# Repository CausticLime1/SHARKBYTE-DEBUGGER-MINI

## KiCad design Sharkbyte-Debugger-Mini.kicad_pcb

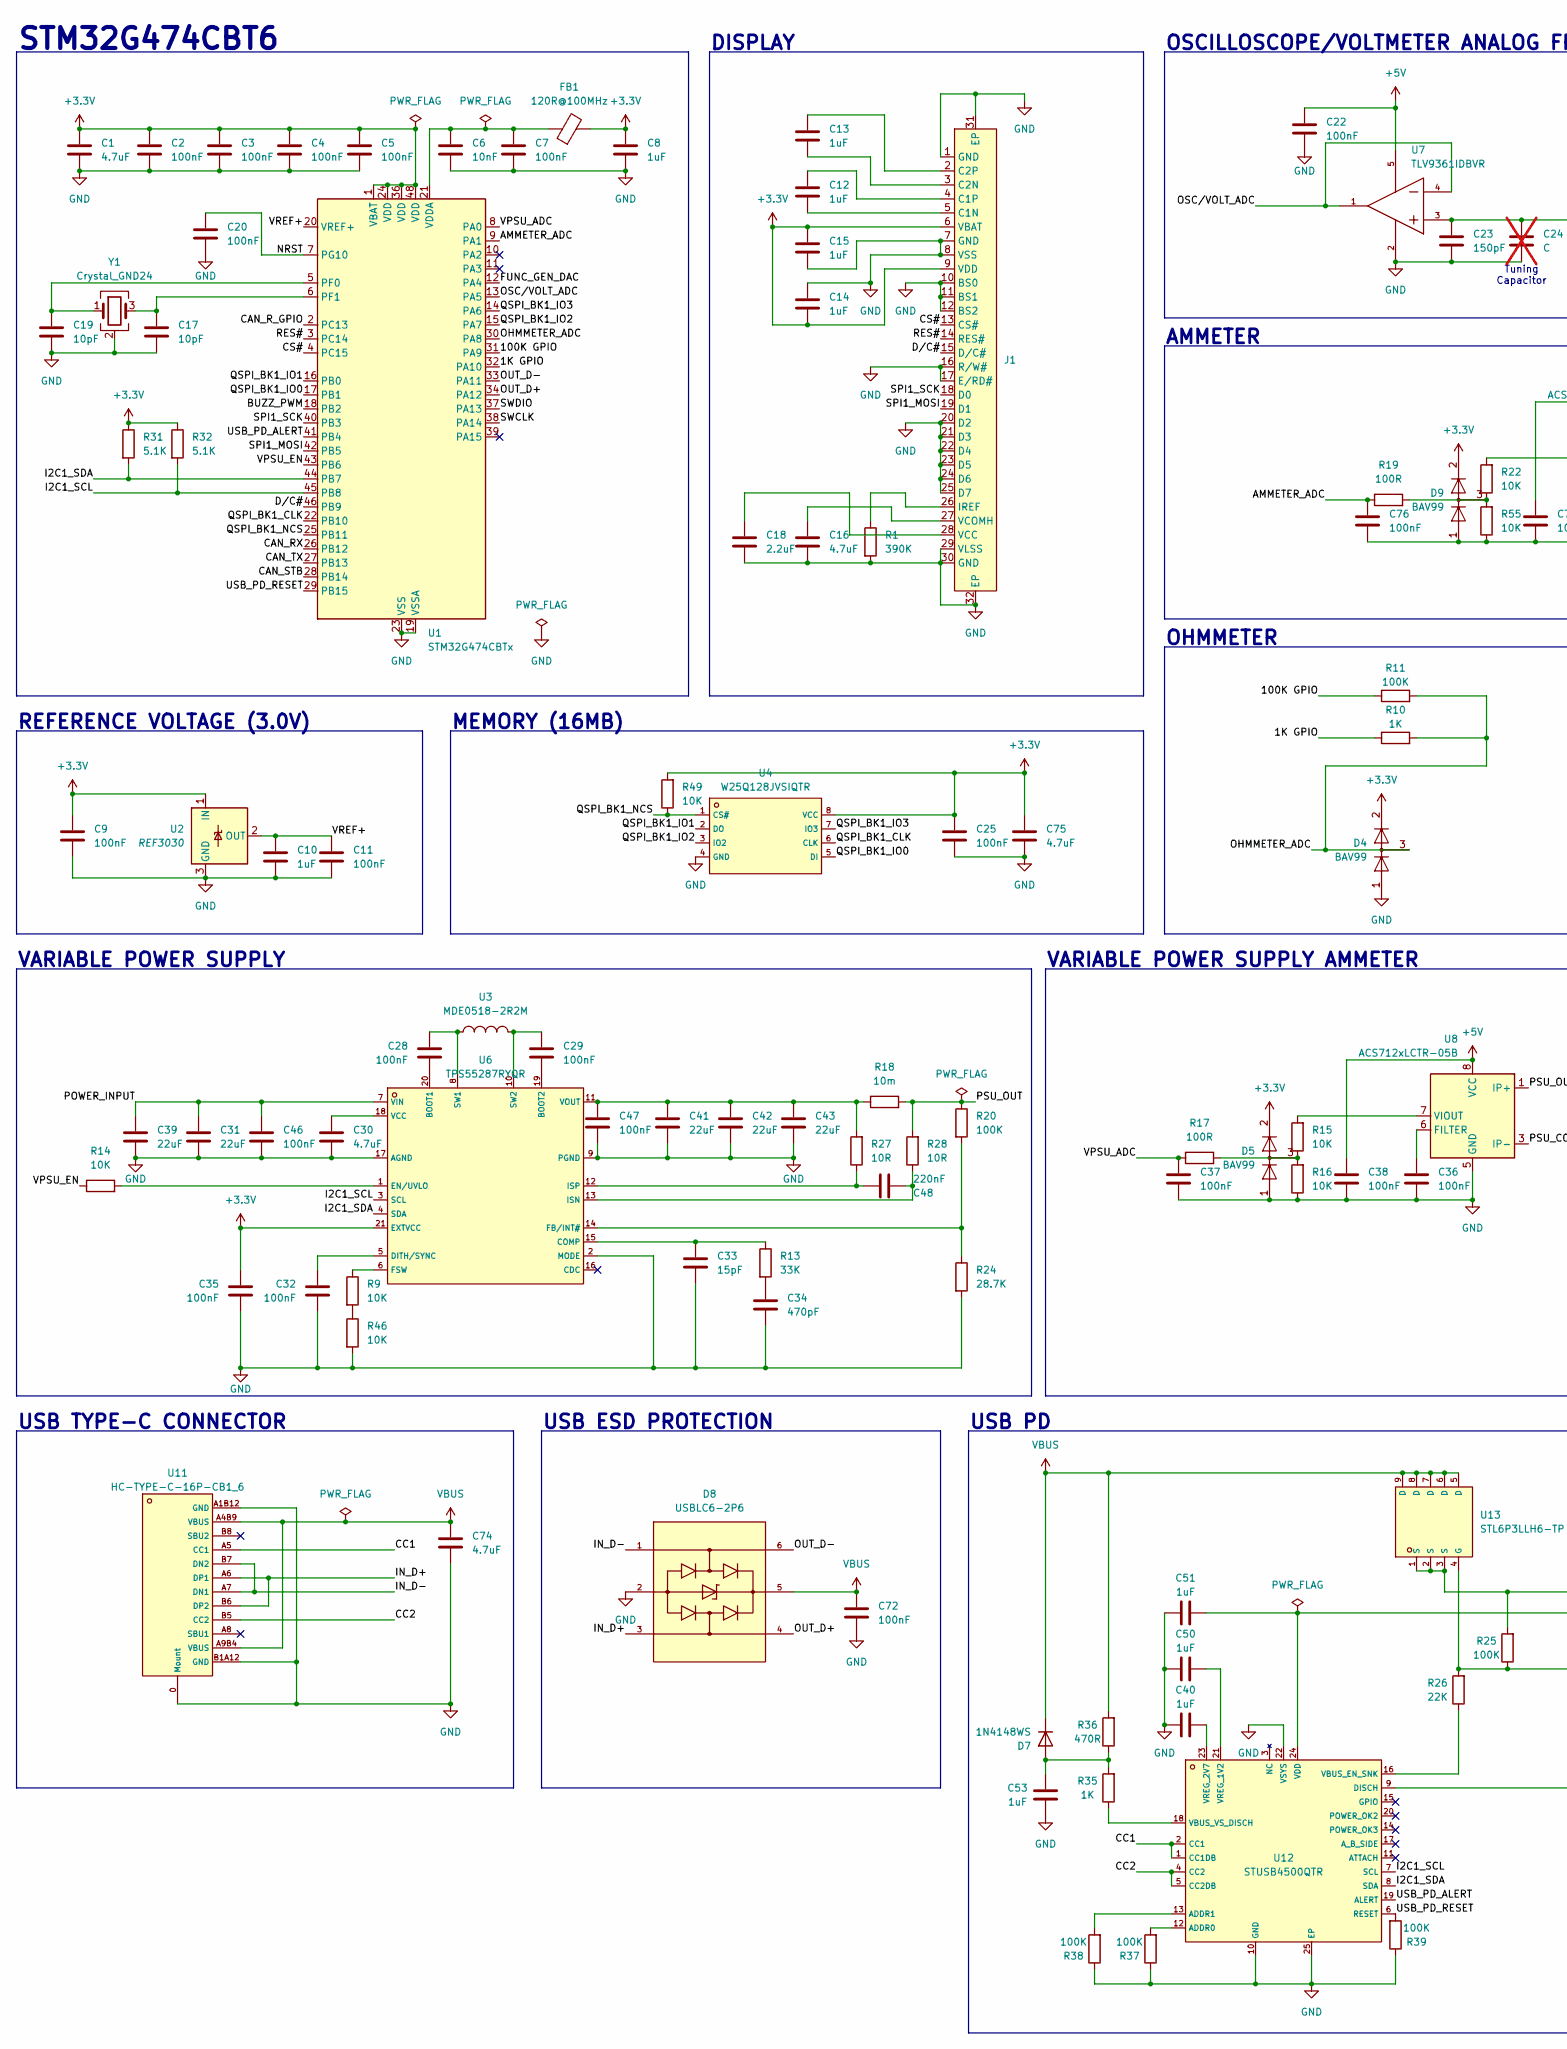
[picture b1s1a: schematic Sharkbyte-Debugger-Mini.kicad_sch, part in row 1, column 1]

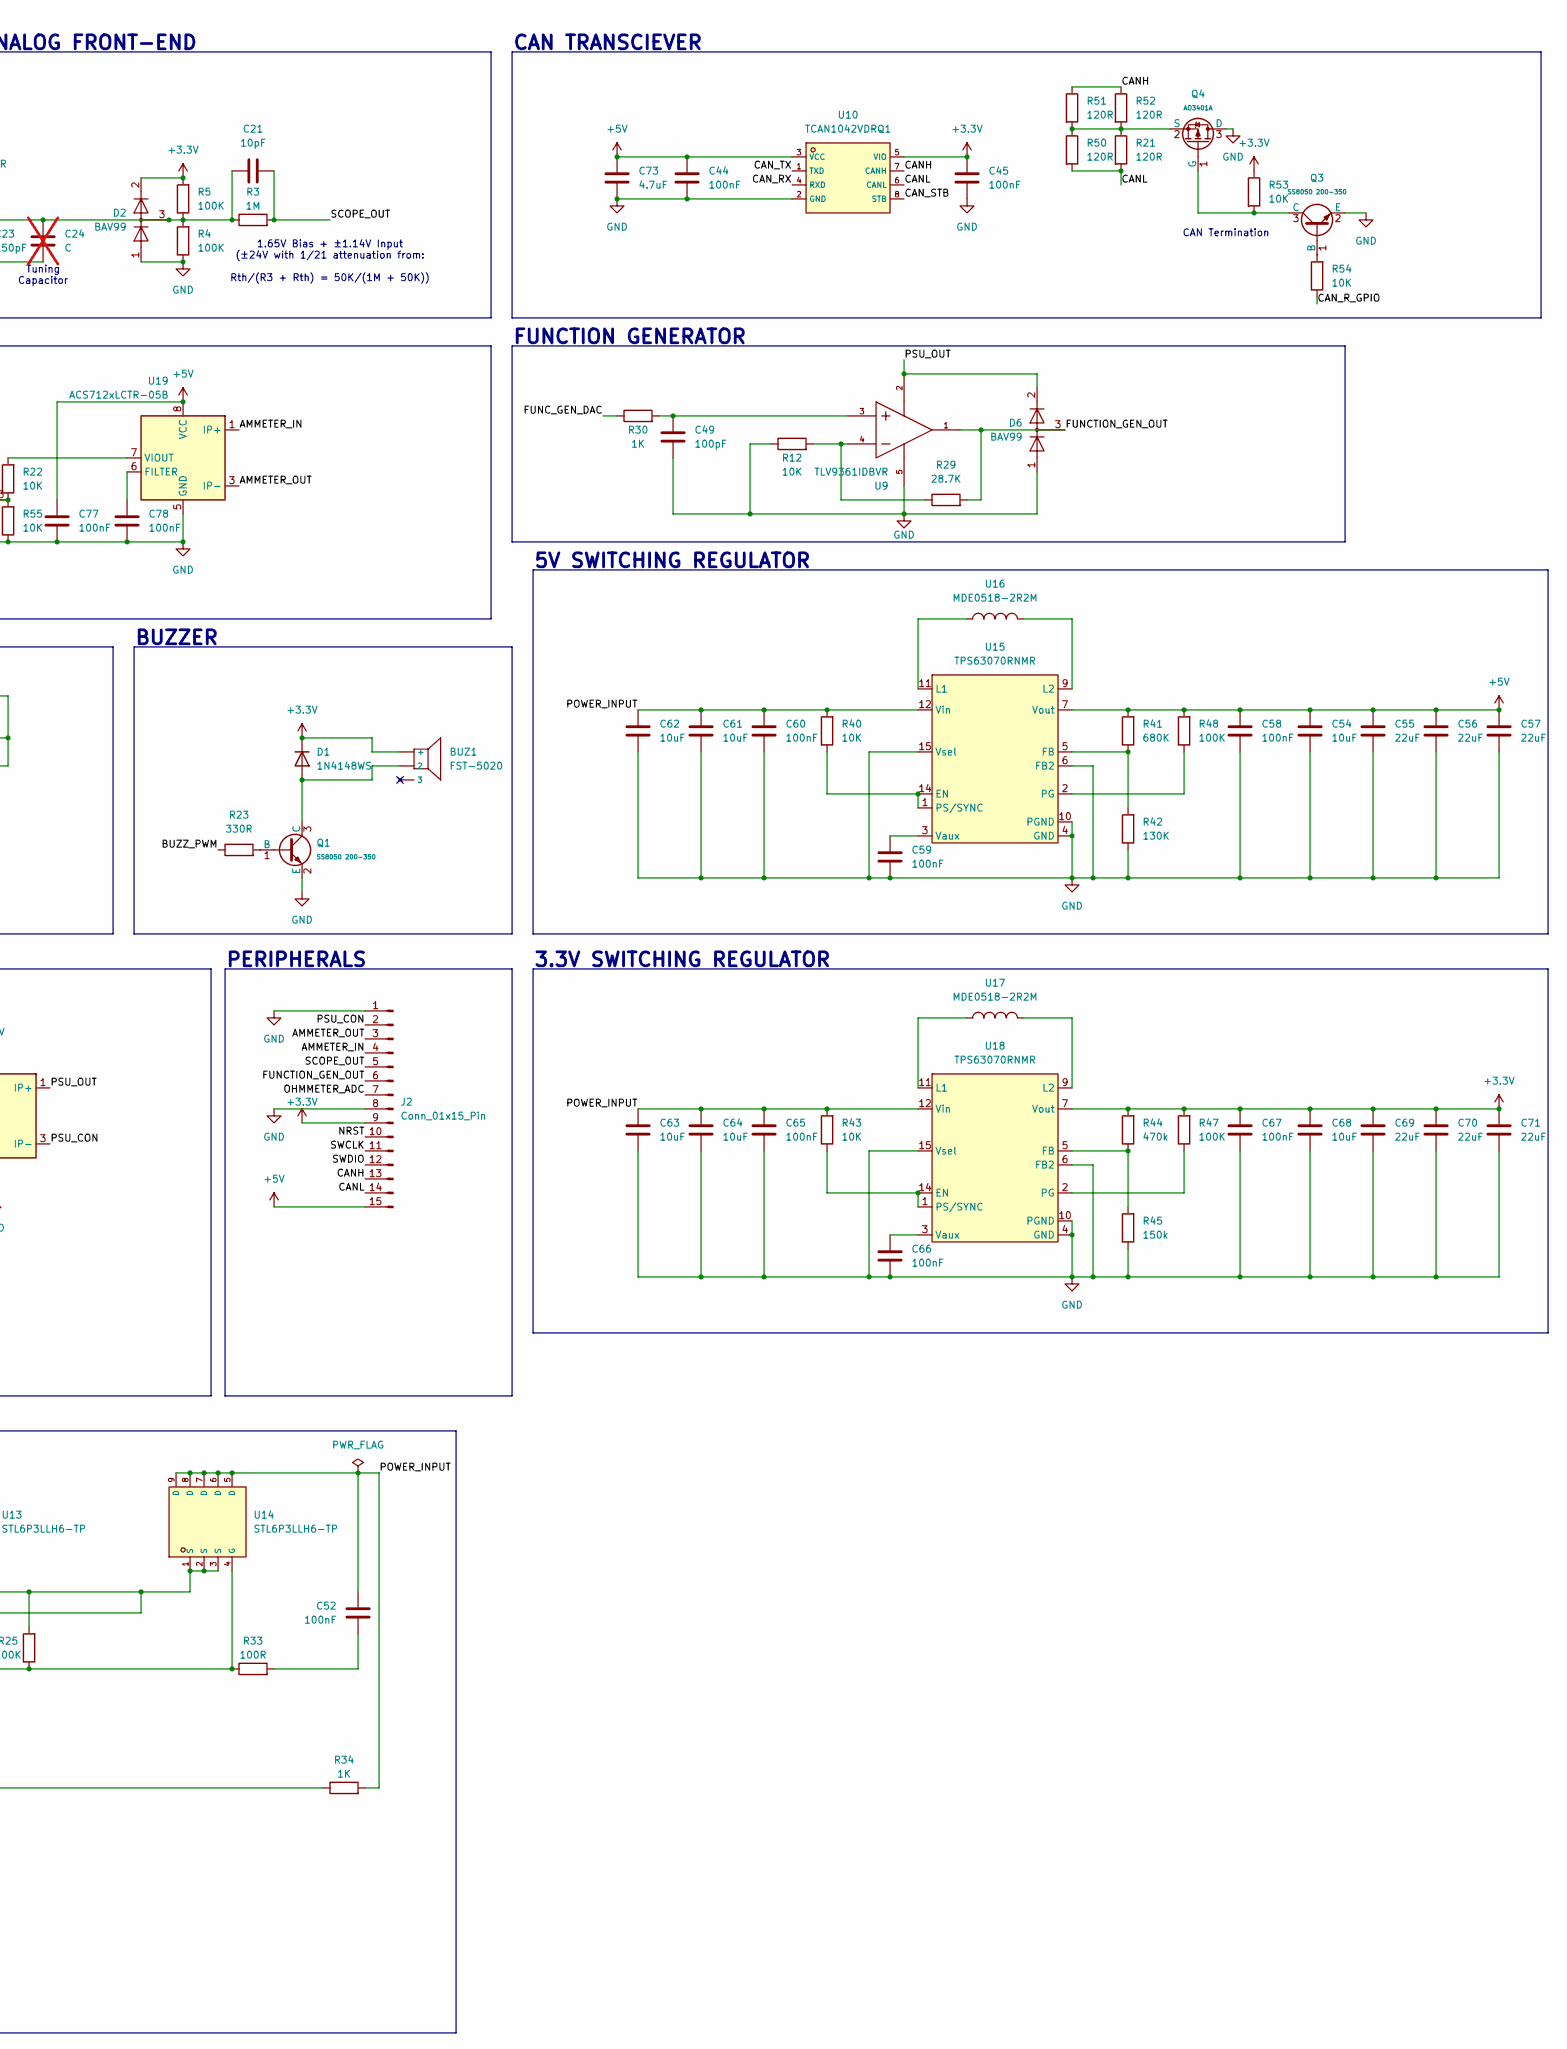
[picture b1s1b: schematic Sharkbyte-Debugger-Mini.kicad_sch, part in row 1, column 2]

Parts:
BUZ1: FST-5020; BUZ-SMD_FST-5020; LCSC C391029
C1, C16, C30, C73, C74, C75: 4.7uF; C_0603
C2, C3, C4, C5, C7, C9, C11, C20, C22, C25, C28, C29, C32, C35, C36, C37, C38, C44, C45, C46, C47, C52, C58, C59, C60, C65, C66, C67, C72, C76, C77, C78: 100nF; C_0402
C6: 10nF; C_0402
C8, C10, C12, C13, C14, C15, C40, C50, C51, C53: 1uF; C_0402
C17, C19, C21: 10pF; C_0402
C18: 2.2uF; C_0603
C23: 150pF; C_0402
C24: C; C_0402; not fitted
C31, C39, C41, C42, C43, C55, C56, C57, C69, C70, C71: 22uF; C_0805
C33: 15pF; C_0402
C34: 470pF; C_0402
C48: 220nF; C_0402
C49: 100pF; C_0402
C54, C61, C62, C63, C64, C68: 10uF; C_0603
D1, D7: 1N4148WS; D_SOD-323
D2: BAV99; SOT-23-3_L2.9-W1.4-P1.90-LS2.5-BR
D4, D5, D6, D9: BAV99; SOT-23
D8: USBLC6-2P6; SOT-666-6_L1.6-W1.2-P0.50-LS1.6-BR; LCSC C15999
FB1: 120R@100MHz; L_0603
J1: ER-CON30HT-1
J2: Conn_01x15_Pin; PinEdgeConn1x15
Q1, Q3: SS8050 200-350; Q_SOT-23; Part SS8050(RANGE:200-350); LCSC C2150
Q4: AO3401A; Q_SOT-23; Part AO3401A; LCSC C15127
R1: 390K; R_0603
R3: 1M; R_0603
R4, R5, R11, R20, R25, R37, R38, R39, R47, R48: 100K; R_0402
R9, R12, R14, R15, R16, R22, R40, R43, R46, R49, R53, R54, R55: 10K; R_0402
R10, R30, R34, R35: 1K; R_0402
R13: 33K; R_0402
R17, R19, R33: 100R; R_0402
R18: 10m; R_1225_3264Metric
R21, R50, R51, R52: 120R; R_0402
R23: 330R; R_0402
R24, R29: 28.7K; R_0402
R26: 22K; R_0402
R27, R28: 10R; R_0402
R31, R32: 5.1K; R_0402
R36: 470R; R_0402
R41: 680K; R_0402
R42: 130K; R_0402
R44: 470k; R_0402
R45: 150k; R_0402
U1: STM32G474CBTx; LQFP-48_7x7mm_P0.5mm
U2: REF3030; SOT-23
U3, U16, U17: MDE0518-2R2M; IND-SMD_L5.4-W5.2; LCSC C2875715
U4: W25Q128JVSIQTR; SOIC-8_L5.3-W5.3-P1.27-LS8.0-BL; LCSC C97521
U6: TPS55287RYQR; VQFN-21_L5.0-W3.0-P0.50-TL; LCSC C41428244
U7, U9: TLV9361IDBVR; SOT-23-5_L2.9-W1.6-P0.95-LS2.8-BR; LCSC C4367444
U8, U19: ACS712xLCTR-05B; SOIC-8_3.9x4.9mm_P1.27mm
U10: TCAN1042VDRQ1; SOIC-8_L4.9-W3.9-P1.27-LS6.0-BL; LCSC C485806
U11: HC-TYPE-C-16P-CB1_6; USB-C-SMD_HC-TYPE-C-16P-CB1.6; LCSC C2894902
U12: STUSB4500QTR; QFN-24_L4.0-W4.0-P0.50-BL-EP2.8; LCSC C2678061
U13, U14: STL6P3LLH6-TP; DFN-8_L3.0-W3.0-P0.65-BL_WPM3028-8; LCSC C49452349
U15, U18: TPS63070RNMR; VQFN-HR-15_L3.0-W2.5-P0.50-BL_TPS63070RNMR; LCSC Part C109322
Y1: Crystal_GND24; Crystal_SMD_3225-4Pin_3.2x2.5mm

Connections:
+3.3V: BUZ1.1 (+), C1.1, C2.1, C3.1, C4.1, C5.1, C8.1, C9.1, C14.2, C15.1, C25.1, C35.1, C45.1, C67.1, C68.1, C69.1, C70.1, C71.1, C75.1, D1.1 (K), D2.2 (A), D4.2 (A), D5.2 (A), D9.2 (A), FB1.2, J1.6 (VBAT), J1.9 (VDD), J2.9, R5.2, R31.1, R32.1, R44.2, R47.2, R49.2, R53.1, U1.1 (VBAT), U1.24 (VDD), U1.36 (VDD), U1.48 (VDD), U2.1 (IN), U4.8 (VCC), U6.21 (EXTVCC), U10.5 (VIO), U18.7 (Vout), U18.8 (Vout)
+5V: C22.1, C38.1, C44.1, C54.1, C55.1, C56.1, C57.1, C58.1, C73.1, C77.1, J2.15, R41.2, R48.2, U7.5 (V+), U8.8 (VCC), U10.3 (VCC), U15.7 (Vout), U15.8 (Vout), U19.8 (VCC)
/1K GPIO: R10.1, U1.32 (PA10)
/100K GPIO: R11.1, U1.31 (PA9)
/AMMETER_ADC: C76.1, R19.1, U1.9 (PA1)
/AMMETER_IN: J2.4, U19.1 (IP+), U19.2 (IP+)
/AMMETER_OUT: J2.3, U19.3 (IP-), U19.4 (IP-)
/BUZZ_PWM: R23.1, U1.18 (PB2)
/CANH: J2.13, R51.1, R52.1, U10.7 (CANH)
/CANL: J2.14, R21.2, R50.2, U10.6 (CANL)
/CAN_RX: U1.26 (PB12), U10.4 (RXD)
/CAN_R_GPIO: R54.1, U1.2 (PC13)
/CAN_STB: U1.28 (PB14), U10.8 (STB)
/CAN_TX: U1.27 (PB13), U10.1 (TXD)
/CC1: U11.A5 (CC1), U12.1 (CC1DB), U12.2 (CC1)
/CC2: U11.B5 (CC2), U12.4 (CC2), U12.5 (CC2DB)
/CS#: J1.13 (CS#), U1.4 (PC15)
/D/C#: J1.15 (D/C#), U1.46 (PB9)
/FUNCTION_GEN_OUT: D6.3 (K), J2.6, R29.2, U9.1 (OUT)
/FUNC_GEN_DAC: R30.1, U1.12 (PA4)
/I2C1_SCL: R32.2, U1.45 (PB8), U6.3 (SCL), U12.7 (SCL)
/I2C1_SDA: R31.2, U1.44 (PB7), U6.4 (SDA), U12.8 (SDA)
/IN_D+: D8.3 (I/O2), U11.A6 (DP1), U11.B6 (DP2)
/IN_D-: D8.1 (I/O1), U11.A7 (DN1), U11.B7 (DN2)
/NRST: C20.1, J2.10, U1.7 (PG10)
/OHMMETER_ADC: D4.3 (K), J2.7, R10.2, R11.2, U1.30 (PA8)
/OSC/VOLT_ADC: U1.13 (PA5), U7.1 (OUT), U7.4 (-IN)
/OUT_D+: D8.4 (I/O2), U1.34 (PA12)
/OUT_D-: D8.6 (I/O1), U1.33 (PA11)
/PSU_CON: J2.2, U8.3 (IP-), U8.4 (IP-)
/PSU_OUT: D6.2 (A), R18.2, R20.1, R28.2, U8.1 (IP+), U8.2 (IP+), U9.2 (V-)
/QSPI_BK1_CLK: U1.22 (PB10), U4.6 (CLK)
/QSPI_BK1_IO0: U1.17 (PB1), U4.5 (DI)
/QSPI_BK1_IO1: U1.16 (PB0), U4.2 (DO)
/QSPI_BK1_IO2: U1.15 (PA7), U4.3 (IO2)
/QSPI_BK1_IO3: U1.14 (PA6), U4.7 (IO3)
/QSPI_BK1_NCS: R49.1, U1.25 (PB11), U4.1 (CS#)
/RES#: J1.14 (RES#), U1.3 (PC14)
/SCOPE_OUT: C21.2, J2.5, R3.2
/SPI1_MOSI: J1.19 (D1), U1.42 (PB5)
/SPI1_SCK: J1.18 (D0), U1.40 (PB3)
/SWCLK: J2.11, U1.38 (PA14)
/SWDIO: J2.12, U1.37 (PA13)
/USB_PD_ALERT: U1.41 (PB4), U12.19 (ALERT)
/USB_PD_RESET: R39.2, U1.29 (PB15), U12.6 (RESET)
/VPSU_ADC: C37.1, R17.1, U1.8 (PA0)
/VPSU_EN: R14.1, U1.43 (PB6)
/VREF+: C10.1, C11.1, U1.20 (VREF+), U2.2 (OUT)
GND: C1.2, C2.2, C3.2, C4.2, C5.2, C6.2, C7.2, C8.2, C9.2, C10.2, C11.2, C14.1, C15.2, C16.2, C17.2, C18.2, C19.2, C20.2, C22.2, C23.1, C24.1, C25.2, C30.2, C31.2, C32.2, C33.2, C34.2, C35.2, C36.2, C37.2, C38.2, C39.2, C40.1, C41.2, C42.2, C43.2, C44.2, C45.2, C46.2, C47.2, C49.2, C50.1, C51.1, C53.1, C54.2, C55.2, C56.2, C57.2, C58.2, C59.2, C60.2, C61.2, C62.2, C63.2, C64.2, C65.2, C66.2, C67.2, C68.2, C69.2, C70.2, C71.2, C72.2, C73.2, C74.2, C75.2, C76.2, C77.2, C78.2, D2.1 (K), D4.1 (K), D5.1 (K), D6.1 (K), D8.2 (GND), D9.1 (K), J1.1 (GND), J1.7 (GND), J1.8 (VSS), J1.10 (BS0), J1.11 (BS1), J1.12 (BS2), J1.16 (R/W#), J1.17 (E/RD#), J1.20 (D2), J1.21 (D3), J1.22 (D4), J1.23 (D5), J1.24 (D6), J1.25 (D7), J1.29 (VLSS), J1.30 (GND), J1.31 (EP), J1.32 (EP), J2.1, J2.8, Q1.2 (E), Q3.2 (E), Q4.3 (D), R1.2, R4.1, R12.1, R16.1, R24.2, R37.1, R38.1, R39.1, R42.1, R45.1, R46.2, R55.1, U1.19 (VSSA), U1.23 (VSS), U1.35 (VSS), U1.47 (VSS), U2.3 (GND), U4.4 (GND), U6.2 (MODE), U6.9 (PGND), U6.17 (AGND), U7.2 (V-), U8.5 (GND), U9.5 (V+), U10.2 (GND), U11.0 (Mount), U11.A1B12 (GND), U11.B1A12 (GND), U12.10 (GND), U12.22 (VSYS), U12.25 (EP), U15.4 (GND), U15.6 (FB2), U15.10 (PGND), U15.15 (Vsel), U18.4 (GND), U18.6 (FB2), U18.10 (PGND), U18.15 (Vsel), U19.5 (GND), Y1.2 (G), Y1.4 (G)
unnamed: C34.1, R13.2
unnamed: C52.2, R33.2
unnamed: BUZ1.2, D1.2 (A), Q1.3 (C)
unnamed: D5.3 (K), R15.1, R16.2, R17.2
unnamed: C53.2, D7.2 (A), R35.2, R36.1
unnamed: D9.3 (K), R19.2, R22.1, R55.2
unnamed: C12.2, J1.5 (C1N)
unnamed: C12.1, J1.4 (C1P)
unnamed: C13.2, J1.3 (C2N)
unnamed: C13.1, J1.2 (C2P)
unnamed: J1.26 (IREF), R1.1
unnamed: C18.1, J1.28 (VCC)
unnamed: C16.1, J1.27 (VCOMH)
unnamed: Q1.1 (B), R23.2
unnamed: Q3.1 (B), R54.2
unnamed: Q3.3 (C), Q4.1 (G), R53.2
unnamed: Q4.2 (S), R21.1, R50.1, R51.2, R52.2
unnamed: R9.2, R46.1
unnamed: C19.1, U1.5 (PF0), Y1.1
unnamed: C17.1, U1.6 (PF1), Y1.3
unnamed: C6.1, C7.1, FB1.1, U1.21 (VDDA)
unnamed: C28.2, U6.20 (BOOT1)
unnamed: C29.2, U6.19 (BOOT2)
unnamed: C33.1, R13.1, U6.15 (COMP)
unnamed: C32.1, U6.5 (DITH/SYNC)
unnamed: R14.2, U6.1 (EN/UVLO)
unnamed: R20.2, R24.1, U6.14 (FB/INT#)
unnamed: R9.1, U6.6 (FSW)
unnamed: C48.2, R28.1, U6.13 (ISN)
unnamed: C48.1, R27.1, U6.12 (ISP)
unnamed: C28.1, U3.1, U6.8 (SW1)
unnamed: C29.1, U3.2, U6.10 (SW2)
unnamed: C30.1, U6.18 (VCC)
unnamed: C41.1, C42.1, C43.1, C47.1, R18.1, R27.2, U6.11 (VOUT)
unnamed: C21.1, C23.2, C24.2, D2.3 (K), R3.1, R4.2, R5.1, U7.3 (+IN)
unnamed: C36.1, U8.6 (FILTER)
unnamed: R15.2, U8.7 (VIOUT)
unnamed: C49.1, R30.2, U9.3 (+IN)
unnamed: R12.2, R29.1, U9.4 (-IN)
unnamed: R37.2, U12.12 (ADDR0)
unnamed: R38.2, U12.13 (ADDR1)
unnamed: R34.1, U12.9 (DISCH)
unnamed: R26.1, U12.16 (VBUS_EN_SNK)
unnamed: R35.1, U12.18 (VBUS_VS_DISCH)
unnamed: C51.2, R25.2, U12.24 (VDD), U13.1 (S), U13.2 (S), U13.3 (S), U14.1 (S), U14.2 (S), U14.3 (S)
unnamed: C50.2, U12.21 (VREG_1V2)
unnamed: C40.2, U12.23 (VREG_2V7)
unnamed: R25.1, R26.2, R33.1, U13.4 (G), U14.4 (G)
unnamed: R40.1, U15.1 (PS/SYNC), U15.14 (EN)
unnamed: R41.1, R42.2, U15.5 (FB)
unnamed: U15.11 (L1), U16.1
unnamed: U15.9 (L2), U16.2
unnamed: R48.1, U15.2 (PG)
unnamed: C59.1, U15.3 (Vaux)
unnamed: R43.1, U18.1 (PS/SYNC), U18.14 (EN)
unnamed: R44.1, R45.2, U18.5 (FB)
unnamed: U17.1, U18.11 (L1)
unnamed: U17.2, U18.9 (L2)
unnamed: R47.1, U18.2 (PG)
unnamed: C66.1, U18.3 (Vaux)
unnamed: C78.1, U19.6 (FILTER)
unnamed: R22.2, U19.7 (VIOUT)
VBUS: C72.1, C74.1, D7.1 (K), D8.5 (VBUS), R36.2, U11.A4B9 (VBUS), U11.A9B4 (VBUS), U13.5 (D), U13.6 (D), U13.7 (D), U13.8 (D), U13.9 (D)
Vin: C31.1, C39.1, C46.1, C52.1, C60.1, C61.1, C62.1, C63.1, C64.1, C65.1, R34.2, R40.2, R43.2, U6.7 (VIN), U14.5 (D), U14.6 (D), U14.7 (D), U14.8 (D), U14.9 (D), U15.12 (Vin), U15.13 (Vin), U18.12 (Vin), U18.13 (Vin)

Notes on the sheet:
BUZZER
OSCILLOSCOPE/VOLTMETER ANALOG FRONT-END
VARIABLE POWER SUPPLY
PERIPHERALS
FUNCTION GENERATOR
CAN Termination
MEMORY (16MB)
REFERENCE VOLTAGE (3.0V)
USB TYPE-C CONNECTOR
STM32G474CBT6
VARIABLE POWER SUPPLY AMMETER
CAN TRANSCIEVER
3.3V SWITCHING REGULATOR
USB PD
Tuning Capacitor
OHMMETER
DISPLAY
AMMETER
USB ESD PROTECTION
5V SWITCHING REGULATOR
1.65V Bias + ±1.14V Input (±24V with 1/21 attenuation from: Rth/(R3 + Rth) = 50K/(1M + 50K))

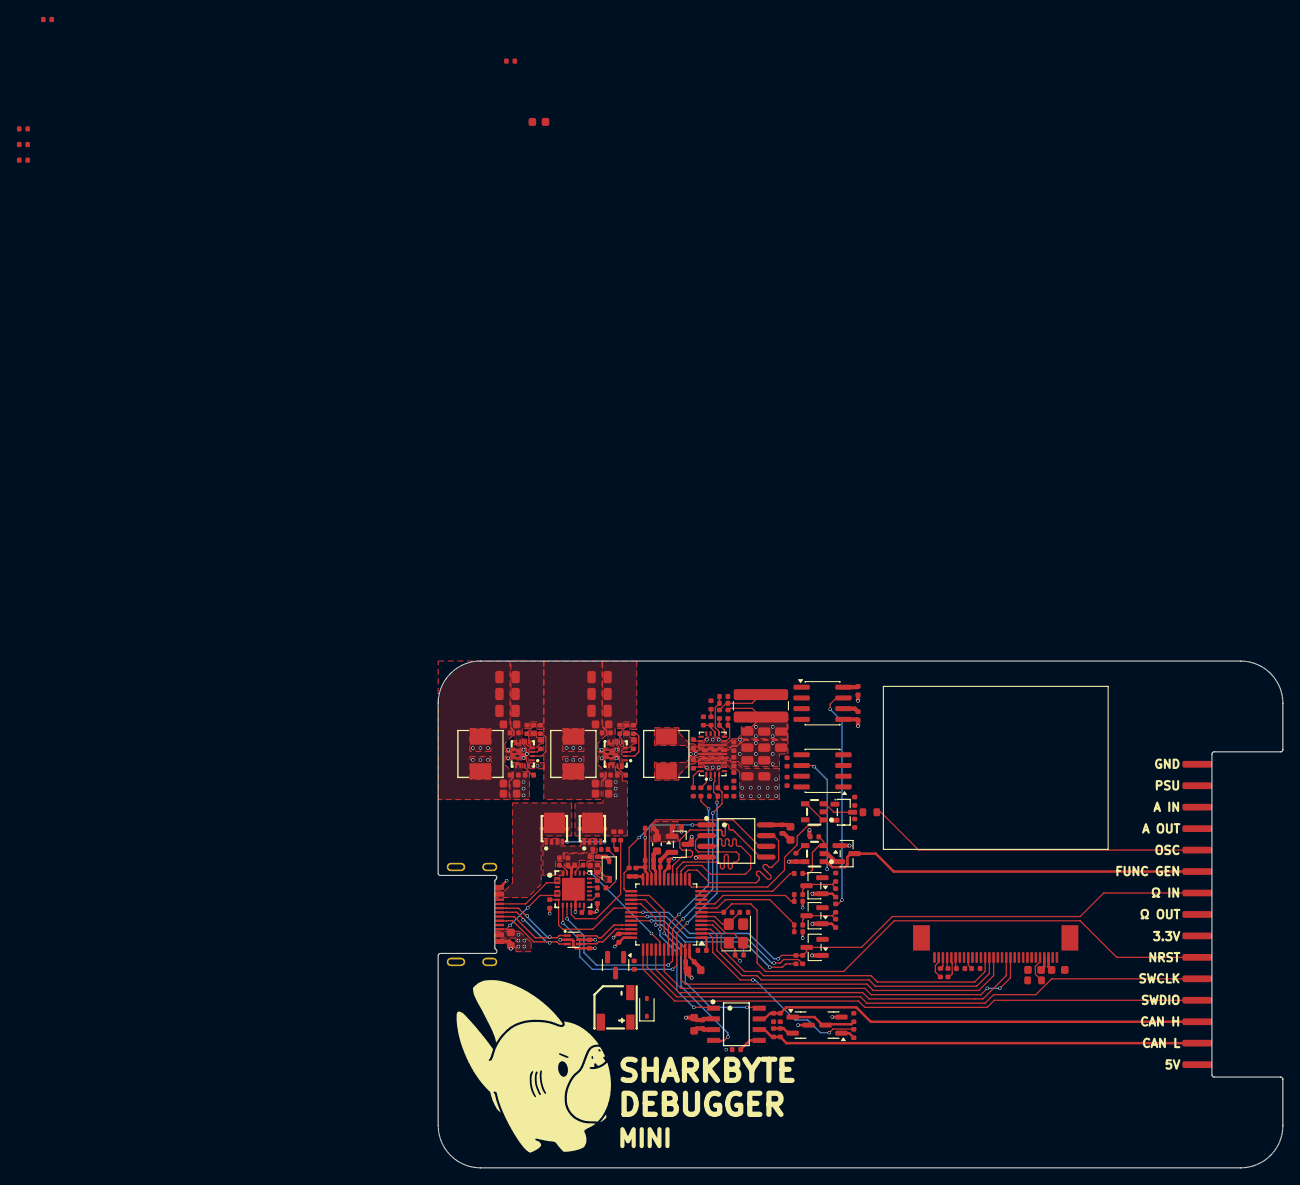
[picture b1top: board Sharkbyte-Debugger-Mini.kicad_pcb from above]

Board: 4 copper layers, 100.0 x 60.0 mm, 161 parts (0 on the bottom side), 113 nets.

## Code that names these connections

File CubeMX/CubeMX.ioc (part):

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Mcu.Name=STM32G474C(B-C-E)Tx
Mcu.Package=LQFP48
Mcu.UserName=STM32G474CBTx
PA0.Mode=IN1-Single-Ended
PA0.Signal=ADC1_IN1
PA1.Mode=IN2-Single-Ended
PA1.Signal=ADC2_IN2
PA10.Signal=GPIO_Output
PA11.Mode=Device
PA11.Signal=USB_DM
PA12.Mode=Device
PA12.Signal=USB_DP
PA13.Mode=Serial_Wire
PA13.Signal=SYS_JTMS-SWDIO
PA14.Mode=Serial_Wire
PA14.Signal=SYS_JTCK-SWCLK
PA2.Signal=S_TIM2_CH3
PA3.Signal=S_TIM2_CH4
PA4.Signal=S_TIM3_CH2
PA5.Signal=COMP_DAC12_group
PA6.Mode=Single Bank 1
PA6.Signal=QUADSPI1_BK1_IO3
PA7.Mode=Single Bank 1
PA7.Signal=QUADSPI1_BK1_IO2
PA8.Mode=IN1-Single-Ended
PA8.Signal=ADC5_IN1
PA9.Signal=GPIO_Output
PB0.Mode=Single Bank 1
PB0.Signal=QUADSPI1_BK1_IO1
PB1.Mode=Single Bank 1
PB1.Signal=QUADSPI1_BK1_IO0
PB10.Mode=Single Bank 1
PB10.Signal=QUADSPI1_CLK
PB11.Mode=Single Bank 1
PB11.Signal=QUADSPI1_BK1_NCS
PB12.Mode=FDCAN_Activate
PB12.Signal=FDCAN2_RX
PB13.Mode=FDCAN_Activate
PB13.Signal=FDCAN2_TX
PB14.Signal=GPIO_Output
PB15.Mode=IN5-Single-Ended
PB15.Signal=ADC4_IN5
PB2.Signal=S_TIM5_CH1
PB3.Mode=Simplex_Bidirectional_Master
PB3.Signal=SPI1_SCK
PB4.Signal=GPXTI4
PB5.Mode=Simplex_Bidirectional_Master
PB5.Signal=SPI1_MOSI
PB6.Signal=GPIO_Output
PB7.Mode=I2C
PB7.Signal=I2C1_SDA
PB8-BOOT0.Mode=I2C
PB8-BOOT0.Signal=I2C1_SCL
PB9.Signal=GPIO_Output
PC13.Signal=GPIO_Output
PC14-OSC32_IN.Signal=GPIO_Output
PC15-OSC32_OUT.Signal=GPIO_Output
PF0-OSC_IN.Mode=HSE-External-Oscillator
PF0-OSC_IN.Signal=RCC_OSC_IN
PF1-OSC_OUT.Mode=HSE-External-Oscillator
PF1-OSC_OUT.Signal=RCC_OSC_OUT
RCC.HSE_VALUE=8000000
RCC.SYSCLKFreq_VALUE=16000000
board=custom
